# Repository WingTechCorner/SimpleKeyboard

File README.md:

# Wing's First Iteration Simple Keyboard

* 2x5 keyswitch layout
* Kailh PG1350 low profile key switches
* 2020 WS2812B RGB led under each key
* Using footprints that allow for swappable keyswitch mounts.
* Added diode for each key switch.
* Added 2.54mm spaced headers for ROW/COL for the key switches and DI/DO/VCC/GND for the LED(s)

# Keyboard Organization

* 2 columns
* 5 rows
* row and column lines brought in in a 2.54mm 1x7 header

# LED Organization

* WS2812B 2020 (2.0x2.0mm) RGB led(s). DIN and DOUT chained in the following manner:

| WS2812B RGB LED  | Position (Row,Col) | Next In Line (Row, Col) |
| :--------------- | :-------:          | :-----:                 |
| LED 1            | (1,1)              | (1,2)                   |
| LED 2            | (1,2)              | (2,1)                   |
| LED 3            | (2,1)              | (2,2)                   |
| LED 4            | (2,2)              | (3,1)                   |
| LED 5            | (3,1)              | (3,2)                   |
| LED 6            | (3,2)              | (4,1)                   |
| LED 7            | (4,1)              | (4,2)                   |
| LED 8            | (4,2)              | (5,1)                   |
| LED 9            | (5,1)              | (5,2)                   |
| LED 10           | (5,2)              | DOUT                    |

# Mounting

* M2.5 mounting holes in the corners
* Inset 2.5mm from edges
* Mount hole plating is electrically connected to GND

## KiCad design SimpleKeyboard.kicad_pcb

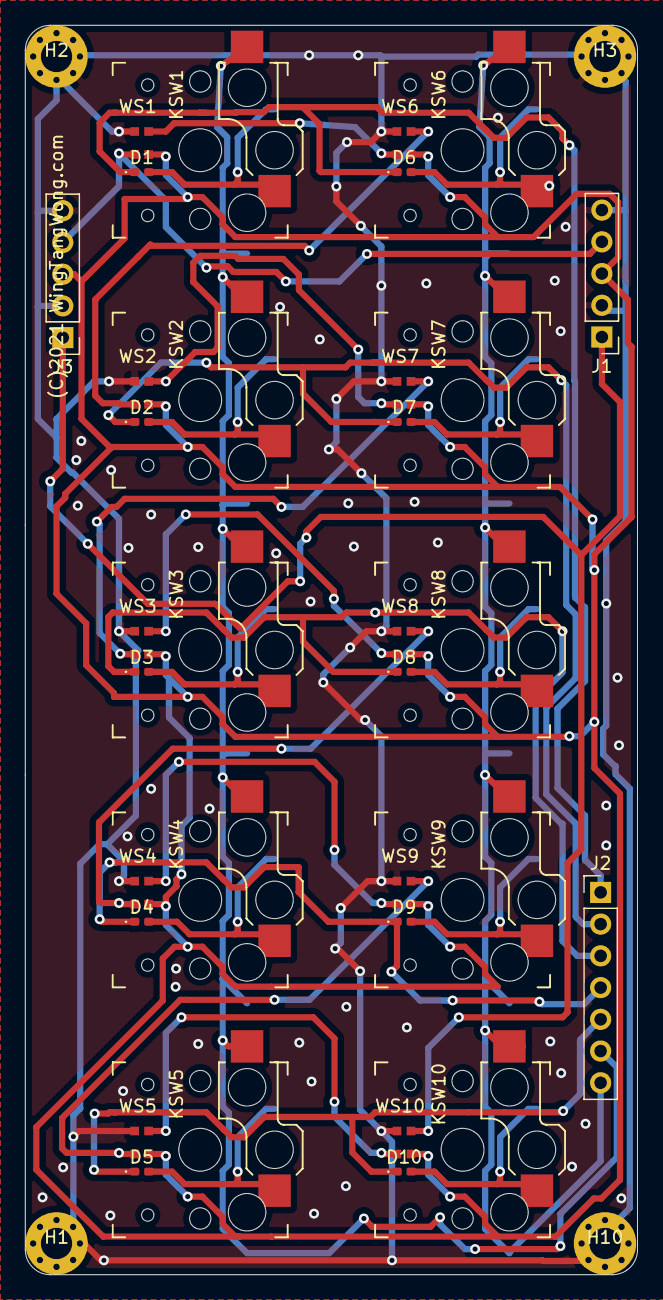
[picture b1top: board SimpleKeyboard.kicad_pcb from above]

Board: 2 copper layers, 49.0 x 100.0 mm, 37 parts (0 on the bottom side), 30 nets.

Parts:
D1, D2, D3, D4, D5, D6, D7, D8, D9, D10: D; D_0402_1005Metric_Pad0.77x0.64mm_HandSolder
H1, H2, H3, H10: MountingHole_Pad; MountingHole_2.5mm_Pad_Via
J1, J3: Conn_01x05; PinHeader_1x05_P2.54mm_Vertical
J2: Conn_01x07; PinHeader_1x07_P2.54mm_Vertical
KSW1, KSW2, KSW3, KSW4, KSW5, KSW6, KSW7, KSW8, KSW9, KSW10: Kailh-Switch; Kailh_socket_PG1350_reversible
WS1, WS2, WS3, WS4, WS5, WS6, WS7, WS8, WS9, WS10: WS2812B-2020-JLCPCB; ws2812b-2020-2.0mmx2.0mm

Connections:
/Sheet6151AA21/COL1: J2.6, KSW1.2, KSW2.2, KSW3.2, KSW4.2, KSW5.2
/Sheet6151AA21/COL2: J2.7, KSW6.2, KSW7.2, KSW8.2, KSW9.2, KSW10.2
/Sheet6151AA21/ROW1: D1.1, D6.1, J2.1
/Sheet6151AA21/ROW2: D2.1, D7.1, J2.2
/Sheet6151AA21/ROW3: D3.1, D8.1, J2.3
/Sheet6151AA21/ROW4: D4.1, D9.1, J2.4
/Sheet6151AA21/ROW5: D5.1, D10.1, J2.5
/Sheet6151AA21/sheet6151C3C0/DI: WS4.3, WS8.1
/Sheet6151AA21/sheet6151C4B7/DI: WS5.3, WS9.1
/Sheet6151AA21/sheet6151C28A/DI: WS3.3, WS7.1
/Sheet6151AA21/sheet6151C193/DI: WS2.3, WS6.1
/Sheet6151AA21/sheet6151D2DE/DI: WS1.1, WS6.3
/Sheet6151AA21/sheet6151D2DF/DI: WS2.1, WS7.3
/Sheet6151AA21/sheet6151D2E0/DI: WS3.1, WS8.3
/Sheet6151AA21/sheet6151D2E1/DI: WS4.1, WS9.3
/Sheet6151AA21/sheet6151D2E2/DI: WS5.1, WS10.3
GND: H1.1, H2.1, H3.1, H10.1, J1.2, J1.5, J3.2, J3.5, WS1.2, WS2.2, WS3.2, WS4.2, WS5.2, WS6.2, WS7.2, WS8.2, WS9.2, WS10.2
LED-IN: J1.4, J3.4, WS1.3
LED-OUT: J1.1, J3.1, WS10.1
unnamed: D1.2, KSW1.1
unnamed: D2.2, KSW2.1
unnamed: D3.2, KSW3.1
unnamed: D4.2, KSW4.1
unnamed: D5.2, KSW5.1
unnamed: D6.2, KSW6.1
unnamed: D7.2, KSW7.1
unnamed: D8.2, KSW8.1
unnamed: D9.2, KSW9.1
unnamed: D10.2, KSW10.1
VCC: J1.3, J3.3, WS1.4, WS2.4, WS3.4, WS4.4, WS5.4, WS6.4, WS7.4, WS8.4, WS9.4, WS10.4

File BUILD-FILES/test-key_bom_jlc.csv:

"Comment","Designator","Footprint","LCSC Part #"
"D","D1,D2,D3,D4,D5,D6,D7,D8,D9,D10","D_0402_1005Metric_Pad0.77x0.64mm_HandSolder","C125059"
"WS2812B-2020-JLCPCB","WS1,WS2,WS3,WS4,WS5,WS6,WS7,WS8,WS9,WS10","ws2812b-2020-2.0mmx2.0mm","C965555"

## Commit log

2021-09-21 init
2021-09-21 Moved files around
2021-09-21 Added readme.md
2021-09-21 Adding render
2021-09-21 Renamed files to match directory name
2021-09-21 sync
2021-09-21 Added more details about board in README
2021-09-23 Clean up firmware folder

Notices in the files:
SimpleKeyboard.kicad_pcb:
(C)2021 WingTangWong.com
